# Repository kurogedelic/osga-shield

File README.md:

# osga-shield

An open hardware platform for creative coding and generative art, designed to work with the [OSGA software platform](https://github.com/kurogedelic/osga).

## Project Structure

```
osga-shield/
├── CLAUDE.md              # Complete setup guide and troubleshooting
├── PROJECT_STRUCTURE.md   # Detailed project organization
├── firmware/              # Raspberry Pi OS configuration and software
│   ├── install.sh        # Complete installation script
│   ├── boot/             # Boot configuration files
│   ├── config/           # System configurations (ALSA, Grove I2C)
│   ├── scripts/          # Hardware initialization scripts
│   └── systemd/          # Auto-start service definitions
├── hardware/              # Hardware design files
│   ├── kicad/            # KiCad schematic and PCB layout
│   ├── bom/              # Bill of Materials
│   ├── fabrication/      # Gerber files for PCB manufacturing
│   └── 3d-models/        # 3D models for enclosure
└── README.md             # This file - project overview
```

📋 See [PROJECT_STRUCTURE.md](PROJECT_STRUCTURE.md) for detailed organization guide.  
🔧 See [CLAUDE.md](CLAUDE.md) for complete setup instructions and troubleshooting.

## Overview

osga-shield is a Raspberry Pi shield that provides a complete hardware interface for audio-visual creative applications. It features physical controls, motion sensing, environmental monitoring, and high-quality audio output.

## Hardware Architecture

```mermaid
graph TD
  RPI["RPi Zero 2 W"]

  subgraph INPUTS
    BTN_A["Button A"]
    BTN_B["Button B"]
    BTN_C["Button C"]
    BTN_R["Rotary Button"]
    ENC["Rotary Encoder"]
    MPU["MPU6050 (Gyro + Accel)"]
    BME["BME280 (Temp / Hum / Pressure)"]
  end

  subgraph OUTPUTS
    DISP["ILI9341 (320x240 SPI LCD)"]
    DAC["PCM5102 (I2S DAC)"]
    SPK["Speaker"]
    HAPTIC["Piezo Haptic"]
  end

  BTN_A --> RPI
  BTN_B --> RPI
  BTN_C --> RPI
  BTN_R --> RPI
  ENC --> RPI
  MPU --> RPI
  BME --> RPI

  RPI --> DISP
  RPI --> DAC
  DAC --> SPK
  RPI --> HAPTIC
```

## Specifications

### Display
- **Controller**: ILI9341
- **Resolution**: 320x240 pixels
- **Interface**: SPI
- **Color**: 16-bit RGB

### Audio
- **DAC**: PCM5102A (I2S)
- **Output**: 3.5mm stereo jack + built-in speaker
- **Sample Rate**: Up to 384kHz
- **Bit Depth**: 32-bit

### Input Controls
- **Buttons**: 2x tactile switches (A, B)
- **Rotary Encoder**: With push button function (Enter)
- **Motion**: MPU6050 6-axis IMU (3-axis gyro + 3-axis accelerometer)

### Expansion
- **Grove Connector**: I²C expansion port for additional sensors/modules
  - Compatible with Seeed Studio Grove ecosystem
  - 3.3V/5V power selectable

### Feedback
- **Haptic**: Piezo element for tactile feedback
- **Visual**: SPI LCD display

### Processing
- **Platform**: Raspberry Pi Zero 2 W
- **Connectivity**: WiFi, Bluetooth

## Pin Mapping (Raspberry Pi Zero 2 WH)

### I²C Buses
| Bus | Component | GPIO Pin | Physical Pin | Function |
|-----|-----------|----------|--------------|----------|
| I²C1 | MPU_SDA | GPIO 2 | Pin 3 | MPU6050 Data |
| I²C1 | MPU_SCL | GPIO 3 | Pin 5 | MPU6050 Clock |
| I²C (SW) | Grove_SDA | GPIO 22 | Pin 15 | Grove Connector Data |
| I²C (SW) | Grove_SCL | GPIO 23 | Pin 16 | Grove Connector Clock |

### Audio (I²S)
| Component | GPIO Pin | Physical Pin | Function |
|-----------|----------|--------------|----------|
| I2S_BCK | GPIO 18 | Pin 12 | Bit Clock |
| I2S_LRCK | GPIO 19 | Pin 35 | Left/Right Clock |
| I2S_IN | GPIO 20 | Pin 38 | Audio Input |
| I2S_OUT | GPIO 21 | Pin 40 | Audio Output (to PCM5102) |

### Display (SPI)
| Component | GPIO Pin | Physical Pin | Function |
|-----------|----------|--------------|----------|
| LCD_CS | GPIO 8 (CE0) | Pin 24 | Chip Select |
| LCD_MISO | GPIO 9 | Pin 21 | Master In Slave Out |
| LCD_MOSI | GPIO 10 | Pin 19 | Master Out Slave In |
| LCD_SCLK | GPIO 11 | Pin 23 | Serial Clock |
| LCD_DC | GPIO 24 | Pin 18 | Data/Command |
| LCD_RESET | GPIO 25 | Pin 22 | Reset |
| LCD_LED | GPIO 12 | Pin 32 | Backlight PWM |

### Input Controls
| Component | GPIO Pin | Physical Pin | Function |
|-----------|----------|--------------|----------|
| Button_A | GPIO 6 | Pin 31 | Button A |
| Button_B | GPIO 5 | Pin 29 | Button B |
| Rotary_CLK | GPIO 16 | Pin 36 | Encoder Clock |
| Rotary_DT | GPIO 13 | Pin 33 | Encoder Data |
| Rotary_Enter | GPIO 26 | Pin 37 | Encoder Button |

### UART (Debug)
| Component | GPIO Pin | Physical Pin | Function |
|-----------|----------|--------------|----------|
| UART_TX | GPIO 14 | Pin 8 | Transmit |
| UART_RX | GPIO 15 | Pin 10 | Receive |

## Software Support

The osga-shield is designed to work seamlessly with:
- **[OSGA](https://github.com/kurogedelic/osga)**: Open Sound & Graphics Appliance platform
- **Raspberry Pi OS**: Standard Linux support
- **Love2D**: For creative coding applications
- **Python**: Via GPIO and device libraries

## Getting Started

1. **Hardware Assembly**
   - Mount the shield on a Raspberry Pi Zero 2 W
   - Connect speaker or headphones to audio output
   - Power via micro USB

2. **Software Installation**
   ```bash
   # Flash Raspberry Pi OS Lite to SD card
   # Boot the Pi and clone this repository
   git clone https://github.com/kurogedelic/osga-shield.git
   cd osga-shield/firmware
   
   # Run installation script
   sudo ./install.sh
   
   # System will reboot and start OSGA automatically
   ```

3. **Test Hardware**
   - Run the hardware test app from OSGA launcher
   - Verify all buttons, encoder, and sensors work

## Development

### Creating Apps
See the [OSGA documentation](https://github.com/kurogedelic/osga#creating-an-app) for app development guidelines.

### Hardware Libraries
- **Python**: Use `RPi.GPIO`, `smbus2` for I2C devices
- **C/C++**: Use `wiringPi` or direct register access
- **Love2D**: Via OSGA's hardware abstraction layer

## License

This hardware design is open source. Schematics and PCB designs will be released under:
- **Hardware**: CERN Open Hardware License v2
- **Software**: LGPL v3 (matching OSGA platform)

## Credits

Designed by Leo Kuroshita from Hugelton Instruments (2025)

## Contributing

Contributions are welcome! Please submit issues and pull requests for:
- Hardware improvements
- Documentation updates
- Example projects
- Bug fixes

## Related Projects

- **[OSGA](https://github.com/kurogedelic/osga)**: The software platform
- **[osga-apps](https://github.com/kurogedelic/osga-apps)**: Community-contributed applications

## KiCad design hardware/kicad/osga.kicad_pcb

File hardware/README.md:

# OSGA Shield Hardware

## Directory Structure

- **kicad/** - KiCad project files (schematic, PCB layout)
- **bom/** - Bill of Materials and component specifications
- **fabrication/** - Gerber files and fabrication outputs
- **3d-models/** - 3D models for enclosure and mechanical design

## Hardware Revision

Current Version: v1.0

## License

Hardware designs are released under CERN Open Hardware License v2

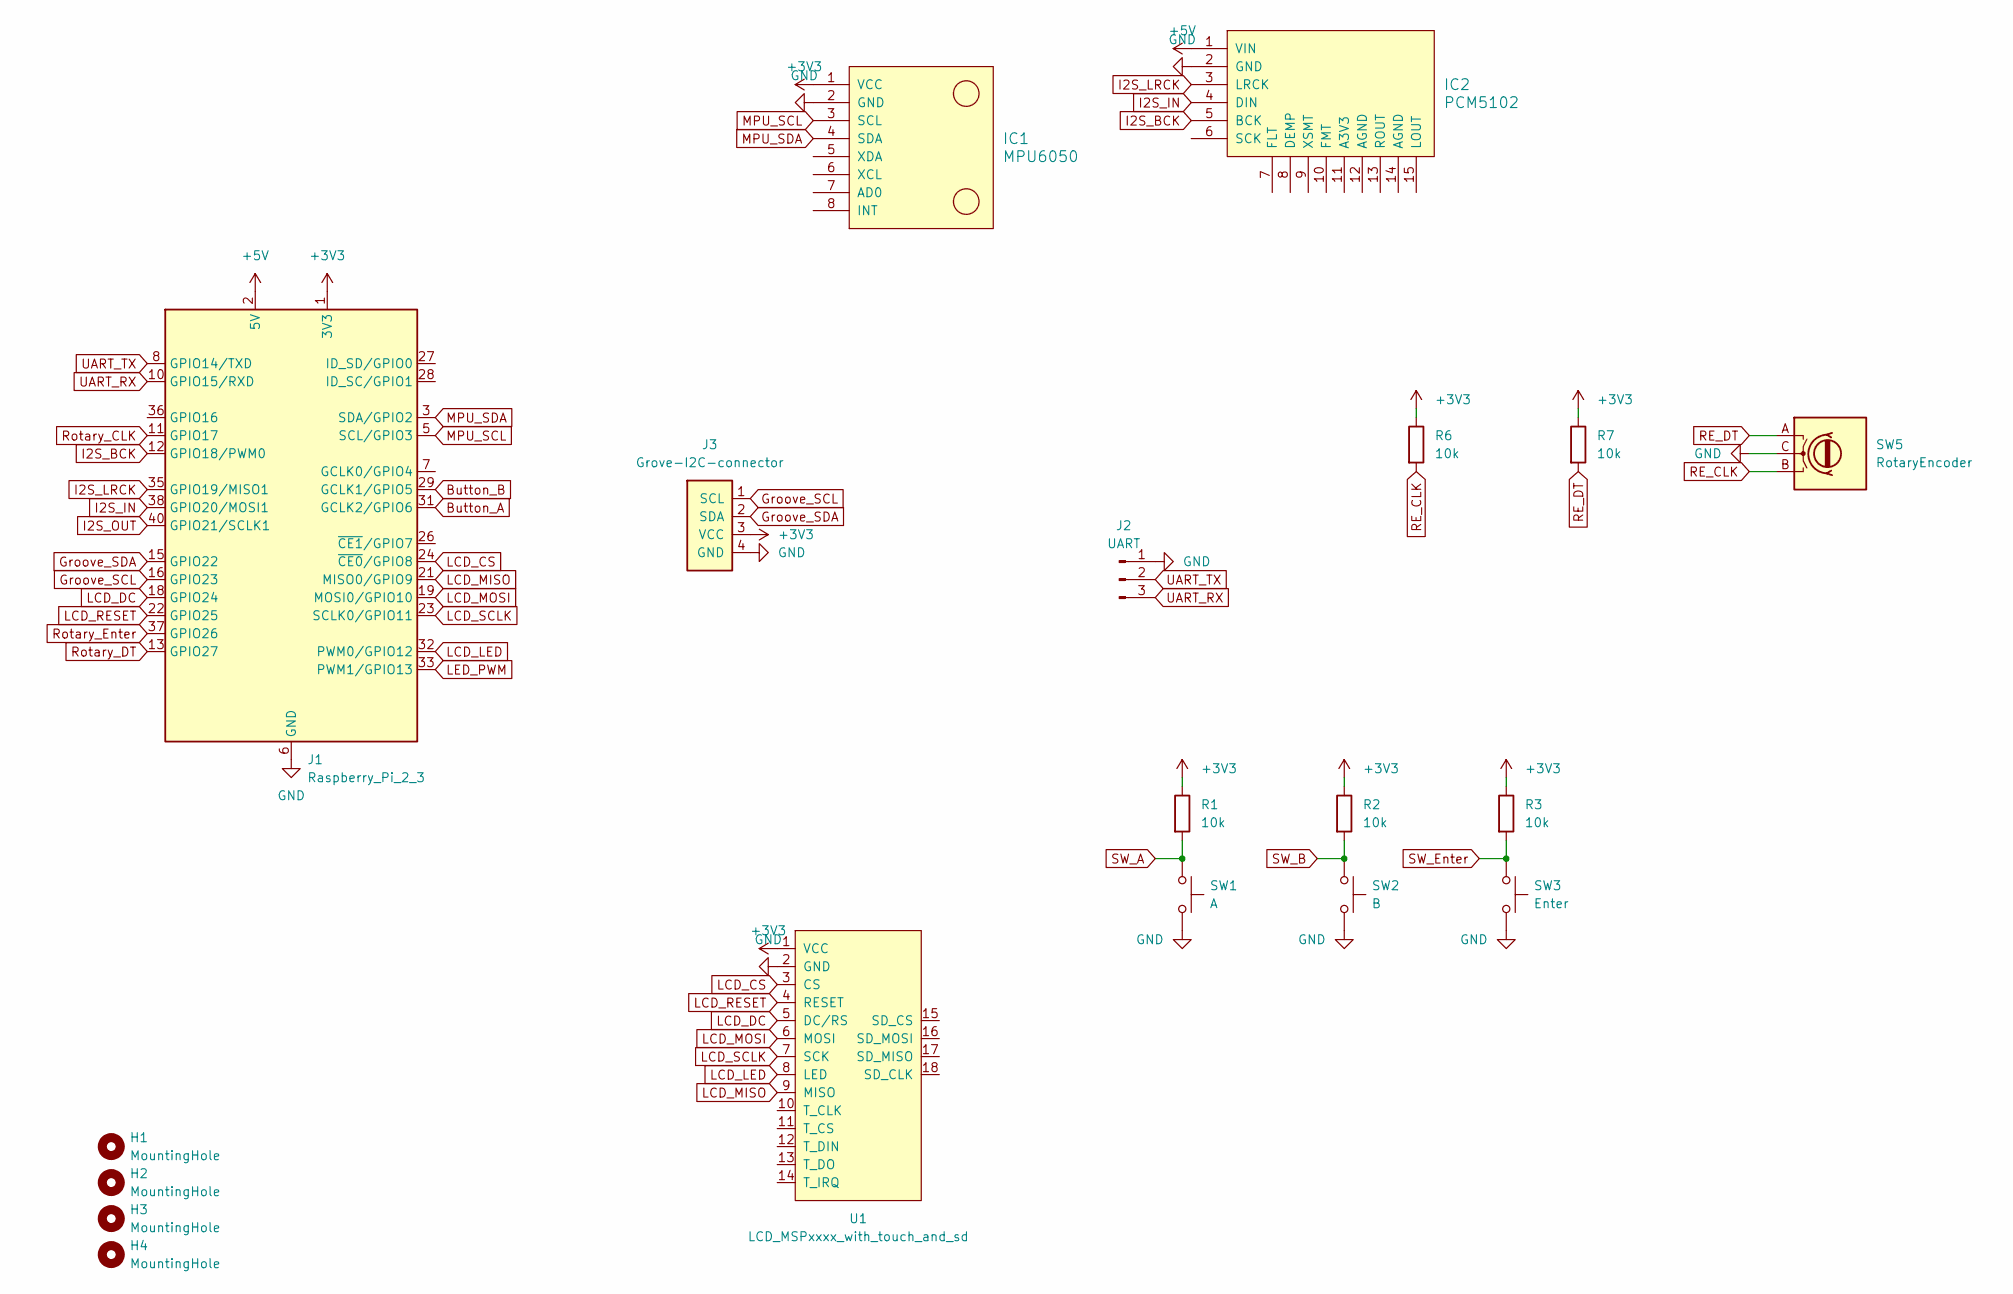
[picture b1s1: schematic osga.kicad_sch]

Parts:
H1, H2, H3, H4: MountingHole; Mounting_Wuerth_WA-SMSI-M2_H1mm_9774010243
IC1: MPU6050
IC2: PCM5102; PCM5102_flipped
J1: Raspberry_Pi_2_3; Raspberry_Pi_Header
J2: UART; PinSocket_1x03_P2.54mm_Horizontal
J3: Grove-I2C-connector; NS-Tech_Grove_1x04_P2mm_Vertical
R1, R2, R3, R6, R7: 10k; R_Axial_DIN0207_L6.3mm_D2.5mm_P10.16mm_Horizontal
SW1: A; SW_Redragon_LowProfile_PCB_1.00u
SW2: B; SW_Redragon_LowProfile_PCB_1.00u
SW3: Enter; SW_Redragon_LowProfile_PCB_1.00u
SW5: RotaryEncoder; RotaryEncoder_Alps_EC12E_Vertical_H20mm
U1: LCD_MSPxxxx_with_touch_and_sd; ili9341_2.4inch

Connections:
+3V3: IC1.1 (VCC), J1.1 (3V3), J1.17 (3V3), J3.3 (VCC), R1.1, R2.1, R3.1, R6.1, R7.1, U1.1 (VCC)
+5V: IC2.1 (VIN), J1.2 (5V), J1.4 (5V)
Button_A: J1.31 (GCLK2/GPIO6)
Button_B: J1.29 (GCLK1/GPIO5)
GND: IC1.2 (GND), IC2.2 (GND), J1.6 (GND), J1.9 (GND), J1.14 (GND), J1.20 (GND), J1.25 (GND), J1.30 (GND), J1.34 (GND), J1.39 (GND), J2.1, J3.4 (GND), SW1.2, SW2.2, SW3.2, SW5.C, U1.2 (GND)
Groove_SCL: J1.16 (GPIO23), J3.1 (SCL)
Groove_SDA: J1.15 (GPIO22), J3.2 (SDA)
I2S_BCK: IC2.5 (BCK), J1.12 (GPIO18/PWM0)
I2S_IN: IC2.4 (DIN), J1.38 (GPIO20/MOSI1)
I2S_LRCK: IC2.3 (LRCK), J1.35 (GPIO19/MISO1)
I2S_OUT: J1.40 (GPIO21/SCLK1)
LCD_CS: J1.24 (~CE0/GPIO8), U1.3 (CS)
LCD_DC: J1.18 (GPIO24), U1.5 (DC/RS)
LCD_LED: J1.32 (PWM0/GPIO12), U1.8 (LED)
LCD_MISO: J1.21 (MISO0/GPIO9), U1.9 (MISO)
LCD_MOSI: J1.19 (MOSI0/GPIO10), U1.6 (MOSI)
LCD_RESET: J1.22 (GPIO25), U1.4 (RESET)
LCD_SCLK: J1.23 (SCLK0/GPIO11), U1.7 (SCK)
LED_PWM: J1.33 (PWM1/GPIO13)
MPU_SCL: IC1.3 (SCL), J1.5 (SCL/GPIO3)
MPU_SDA: IC1.4 (SDA), J1.3 (SDA/GPIO2)
RE_CLK: R6.2, SW5.B
RE_DT: R7.2, SW5.A
Rotary_CLK: J1.11 (GPIO17)
Rotary_DT: J1.13 (GPIO27)
Rotary_Enter: J1.37 (GPIO26)
SW_A: R1.2, SW1.1
SW_B: R2.2, SW2.1
SW_Enter: R3.2, SW3.1
UART_RX: J1.10 (GPIO15/RXD), J2.3
UART_TX: J1.8 (GPIO14/TXD), J2.2

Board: 2 copper layers, 19 parts (2 on the bottom side), 24 nets, no tracks yet.

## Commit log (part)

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2025-08-08 Add .gitignore for .DS_Store files
